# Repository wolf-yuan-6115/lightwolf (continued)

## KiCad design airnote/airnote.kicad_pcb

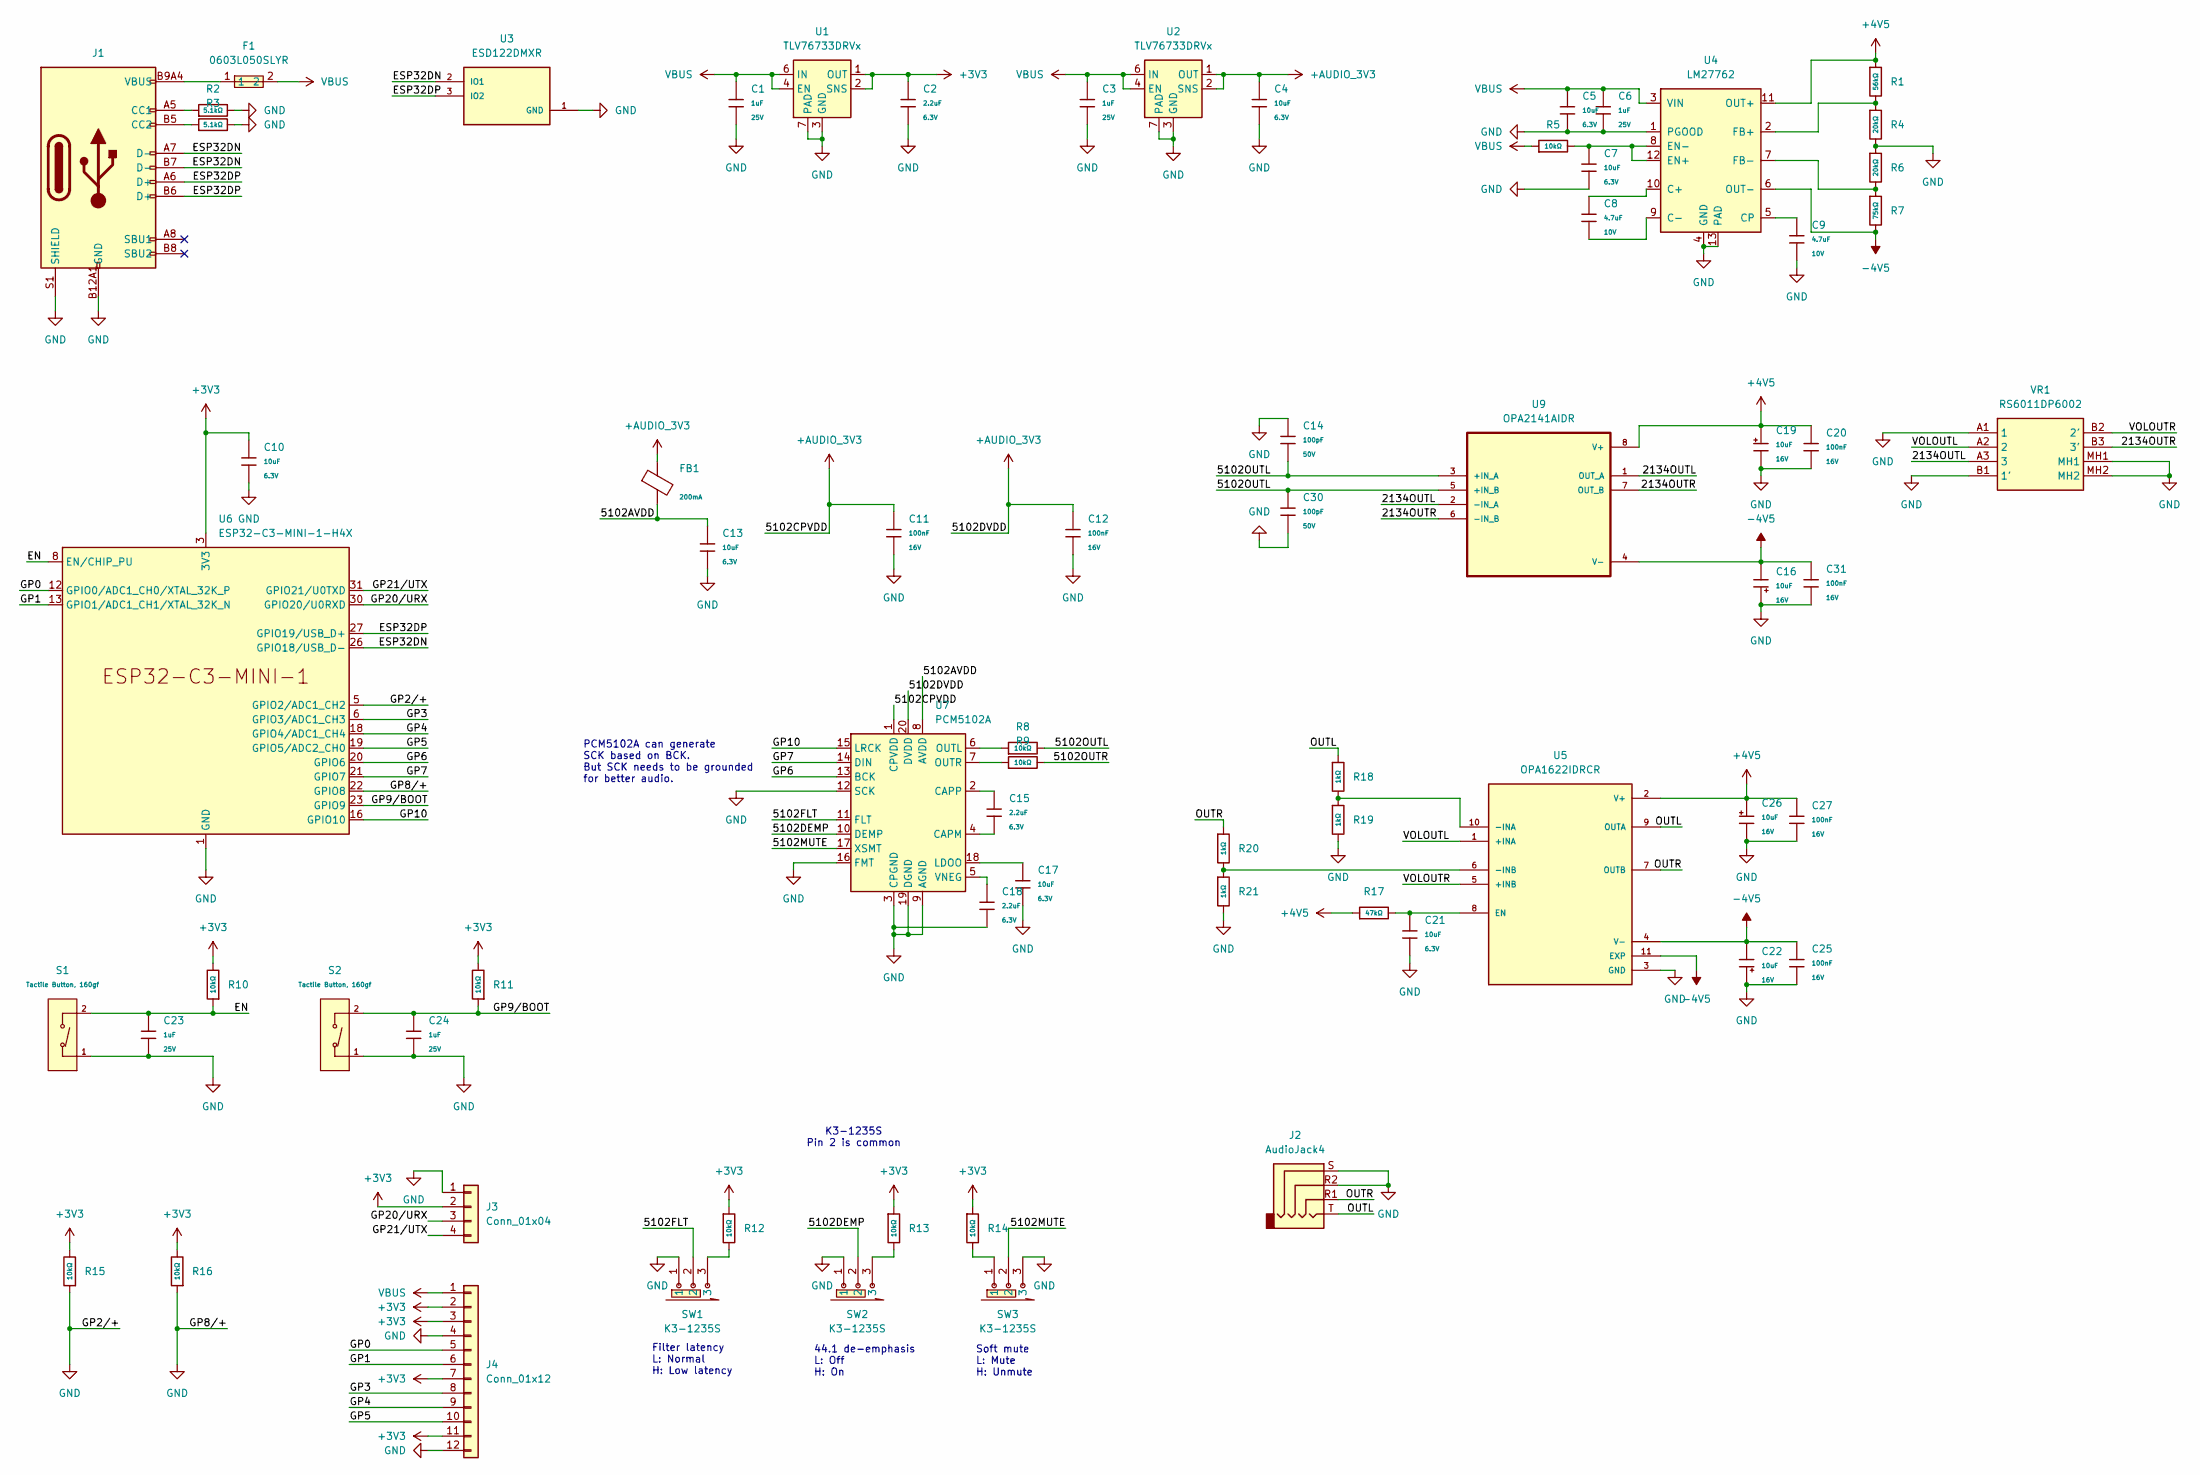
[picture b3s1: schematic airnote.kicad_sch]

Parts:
C1, C3, C6, C23, C24: 1uF; C_0402; Voltage Rated 25V; Tolerance ±10%; Part CL05A105KA5NQNC; LCSC C52923
C2, C15, C18: 2.2uF; C_0402; Voltage Rated 6.3V; Tolerance ±20%; Part CL05A225MQ5NSNC; LCSC C12530
C4, C5, C7, C10, C13, C17, C21: 10uF; C_0402; Voltage Rated 6.3V; Tolerance ±20%; Part CL05A106MQ5NUNC; LCSC C15525
C8, C9: 4.7uF; C_0402; Voltage Rated 10V; Tolerance ±20%; Part CL05A475MP5NRNC; LCSC C23733
C11, C12, C20, C25, C27, C31: 100nF; C_0402; Voltage Rated 16V; Tolerance ±10%; Part CL05B104KO5NNNC; LCSC C1525
C14, C30: 100pF; C_0402; Voltage Rated 50V; Tolerance ±5%; Part 0402CG101J500NT; LCSC C1546
C16, C19, C22, C26: 10uF; C_CASE-A-3216-18(mm); Tolerance ±10%; Rated Voltage 16V; Part TAJA106K016RNJ; LCSC C7171
F1: 0603L050SLYR; F0603; LCSC Part C207014
FB1: FB_0603; Current Rating 200mA; Tolerance ±25%; Part GZ1608D601TF; LCSC C1002
J1: Connector, USB-TYPE-C-16P; TYPE-C-SMD_HX-TYPE-C-16PIN; LCSC C5178539
J2: AudioJack4; Jack_3.5mm_KoreanHropartsElec_PJ-320D-4A_Horizontal
J3: Conn_01x04; PinHeader_1x04_P2.54mm_Vertical; LCSC C41425307
J4: Conn_01x12; PinHeader_1x12_P2.54mm_Vertical; LCSC C725944
R1: 56kΩ; R_0402; Overload Voltage (Max) 50V; Tolerance ±1%; Part 0402WGF5602TCE; LCSC C25796
R2, R3: 5.1kΩ; R_0402; Overload Voltage (Max) 50V; Tolerance ±1%; Part 0402WGF5101TCE; LCSC C25905
R4, R6: 20kΩ; R_0402; Overload Voltage (Max) 50V; Tolerance ±1%; Part 0402WGF2002TCE; LCSC C25765
R5, R8, R9, R10, R11, R12, R13, R14, R15, R16: 10kΩ; R_0402; Overload Voltage (Max) 50V; Tolerance ±1%; Part 0402WGF1002TCE; LCSC C25744
R7: 75kΩ; R_0402; Overload Voltage (Max) 50V; Tolerance ±1%; Part 0402WGF7502TCE; LCSC C25798
R17: 47kΩ; R_0402; Overload Voltage (Max) 50V; Tolerance ±1%; Part 0402WGF4702TCE; LCSC C25792
R18, R19, R20, R21: 1kΩ; R_0402; Overload Voltage (Max) 50V; Tolerance ±1%; Part 0402WGF1001TCE; LCSC C11702
S1, S2: Tactile Button, 160gf; SW_TS-1088-AR02016; Voltage Rating (Dc) 12V; Part TS-1088-AR02016; LCSC C720477
SW1, SW2, SW3: K3-1235S; SW-SMD_K3-1235S-K1; LCSC Part C92660
U1, U2: TLV76733DRVx; WSON-6-1EP_2x2mm_P0.65mm_EP1x1.6mm_ThermalVias
U3: ESD122DMXR; IC_ESD122DMXR; PARTREV A
U4: LM27762; WSON-12-1EP_3x2mm_P0.5mm_EP1x2.65_ThermalVias
U5: OPA1622IDRCR; IC_OPA1622IDRCR; PARTREV B; DigiKey_Part_Number 296-45038-1-ND
U6: ESP32-C3-MINI-1-H4X; ESP32-C3-MINI-1; LCSC C41349510
U7: PCM5102A; TSSOP-20_4.4x6.5mm_P0.65mm
U9: OPA2141AIDR; SOIC127P599X175-8N; DigiKey_Part_Number 296-41347-1-ND
VR1: RS6011DP6002; Mouser Part Number 688-RS6011DP6002

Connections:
+3V3: C2.1, C10.1, J3.2, J4.2, J4.3, J4.7, J4.11, R10.2, R11.2, R12.1, R13.1, R14.1, R15.2, R16.2, U1.1 (OUT), U1.2 (SNS), U6.3 (3V3)
+4V5: C19.1, C20.1, C26.1, C27.1, R1.1, R17.1, U4.11 (OUT+), U5.2 (V+), U9.8 (V+)
+AUDIO_3V3: C4.1, C11.1, C12.1, FB1.1, U2.1 (OUT), U2.2 (SNS), U7.1 (CPVDD), U7.20 (DVDD)
-4V5: C16.2, C22.2, C25.1, C31.1, R7.2, U4.6 (OUT-), U5.4 (V-), U5.11 (EXP), U5.12 (EXP), U5.13 (EXP), U5.14 (EXP), U5.15 (EXP), U9.4 (V-)
/2134OUTL: U9.1 (OUT_A), U9.2 (-IN_A), VR1.A3 (3)
/2134OUTR: U9.6 (-IN_B), U9.7 (OUT_B), VR1.B3 (3')
/5102AVDD: C13.1, FB1.2, U7.8 (AVDD)
/5102DEMP: SW2.2, U7.10 (DEMP)
/5102FLT: SW1.2, U7.11 (FLT)
/5102MUTE: SW3.2, U7.17 (XSMT)
/5102OUTL: C14.1, C30.2, R8.2, U9.3 (+IN_A), U9.5 (+IN_B)
/5102OUTR: R9.2
/EN: C23.1, R10.1, S1.2 (B), U6.8 (EN/CHIP_PU)
/ESP32DN: J1.A7 (D-), J1.B7 (D-), U3.2 (IO1), U6.26 (GPIO18/USB_D-)
/ESP32DP: J1.A6 (D+), J1.B6 (D+), U3.3 (IO2), U6.27 (GPIO19/USB_D+)
/GP0: J4.5, U6.12 (GPIO0/ADC1_CH0/XTAL_32K_P)
/GP1: J4.6, U6.13 (GPIO1/ADC1_CH1/XTAL_32K_N)
/GP3: J4.8, U6.6 (GPIO3/ADC1_CH3)
/GP4: J4.9, U6.18 (GPIO4/ADC1_CH4)
/GP5: J4.10, U6.19 (GPIO5/ADC2_CH0)
/GP6: U6.20 (GPIO6), U7.13 (BCK)
/GP7: U6.21 (GPIO7), U7.14 (DIN)
/GP9/BOOT: C24.1, R11.1, S2.2 (B), U6.23 (GPIO9)
/GP10: U6.16 (GPIO10), U7.15 (LRCK)
/GP20/URX: J3.3, U6.30 (GPIO20/U0RXD)
/GP21/UTX: J3.4, U6.31 (GPIO21/U0TXD)
/OUTL: J2.T, R18.1, U5.9 (OUTA)
/OUTR: J2.R1, R20.1, U5.7 (OUTB)
/VOLOUTL: U5.1 (+INA), VR1.A2 (2)
/VOLOUTR: U5.5 (+INB), VR1.B2 (2')
GND: C1.2, C2.2, C3.2, C4.2, C5.2, C6.2, C7.2, C9.2, C10.2, C11.2, C12.2, C13.2, C14.2, C16.1, C17.2, C18.2, C19.2, C20.2, C21.2, C22.1, C23.2, C24.2, C25.2, C26.2, C27.2, C30.1, C31.2, J1.A12B1 (GND), J1.B12A1 (GND), J1.S1 (SHIELD), J2.R2, J2.S, J3.1, J4.4, J4.12, R2.2, R3.2, R4.2, R6.1, R15.1, R16.1, R19.2, R21.2, S1.1 (A), S2.1 (A), SW1.1, SW2.1, SW3.3, U1.3 (GND), U1.5 (GND), U1.7 (PAD), U2.3 (GND), U2.5 (GND), U2.7 (PAD), U3.1 (GND), U4.1 (PGOOD), U4.4 (GND), U4.13 (PAD), U5.3 (GND), U6.1 (GND), U6.2 (GND), U6.5 (GPIO2/ADC1_CH2), U6.11 (GND), U6.14 (GND), U6.22 (GPIO8), U6.36 (GND), U6.37 (GND), U6.38 (GND), U6.39 (GND), U6.40 (GND), U6.41 (GND), U6.42 (GND), U6.43 (GND), U6.44 (GND), U6.45 (GND), U6.46 (GND), U6.47 (GND), U6.48 (GND), U6.49 (GND), U6.50 (GND), U6.51 (GND), U6.52 (GND), U6.53 (GND), U7.3 (CPGND), U7.9 (AGND), U7.12 (SCK), U7.16 (FMT), U7.19 (DGND), VR1.A1 (1), VR1.B1 (1'), VR1.MH1, VR1.MH2
unnamed: F1.1, J1.A9B4 (VBUS), J1.B9A4 (VBUS)
unnamed: J1.A5 (CC1), R2.1
unnamed: J1.B5 (CC2), R3.1
unnamed: R12.2, SW1.3
unnamed: R13.2, SW2.3
unnamed: R14.2, SW3.1
unnamed: C8.1, U4.10 (C+)
unnamed: C8.2, U4.9 (C-)
unnamed: C9.1, U4.5 (CP)
unnamed: C7.1, R5.2, U4.8 (EN-), U4.12 (EN+)
unnamed: R1.2, R4.1, U4.2 (FB+)
unnamed: R6.2, R7.1, U4.7 (FB-)
unnamed: R18.2, R19.1, U5.10 (-INA)
unnamed: R20.2, R21.1, U5.6 (-INB)
unnamed: C21.1, R17.2, U5.8 (EN)
unnamed: C15.2, U7.4 (CAPM)
unnamed: C15.1, U7.2 (CAPP)
unnamed: C17.1, U7.18 (LDOO)
unnamed: R8.1, U7.6 (OUTL)
unnamed: R9.1, U7.7 (OUTR)
unnamed: C18.1, U7.5 (VNEG)
VBUS: C1.1, C3.1, C5.1, C6.1, F1.2, J4.1, R5.1, U1.4 (EN), U1.6 (IN), U2.4 (EN), U2.6 (IN), U4.3 (VIN)

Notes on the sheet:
44.1 de-emphasis L: Off H: On
Soft mute L: Mute H: Unmute
K3-1235S Pin 2 is common
Filter latency L: Normal H: Low latency
PCM5102A can generate SCK based on BCK. But SCK needs to be grounded for better audio.

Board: 4 copper layers, 70 parts (0 on the bottom side), 52 nets, no tracks yet.

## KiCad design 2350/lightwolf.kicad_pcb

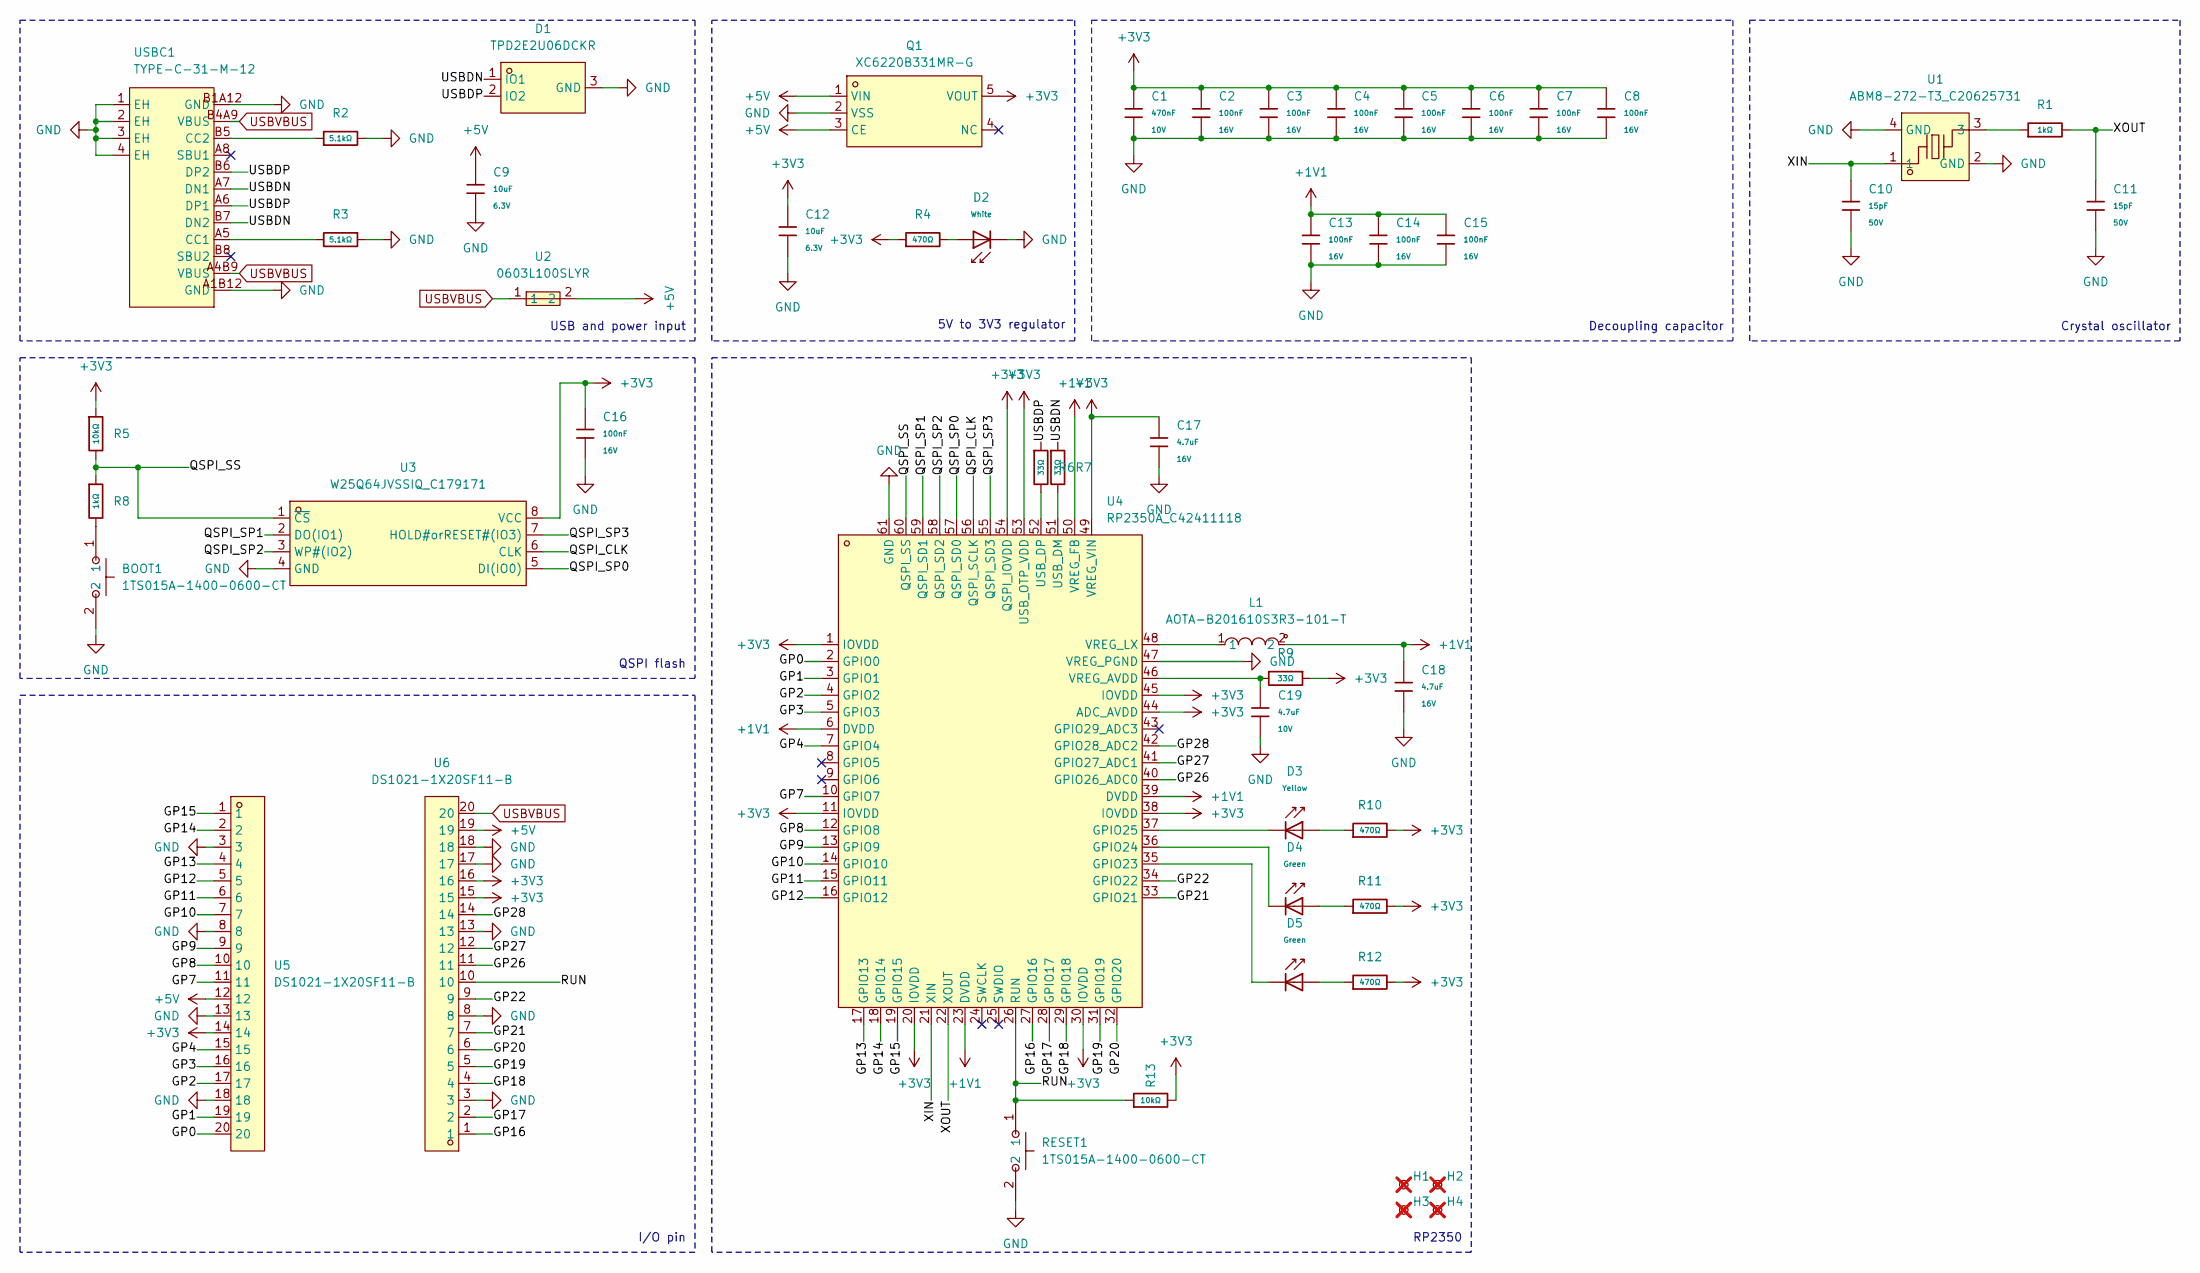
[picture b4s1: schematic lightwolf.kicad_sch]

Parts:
BOOT1: 1TS015A-1400-0600-CT; SW-SMD_L3.0-W2.0-LS3.5; LCSC Part C319433
C1: 470nF; C_0402; Voltage Rated 10V; Tolerance ±10%; Part CL05A474KP5NNNC; LCSC C47339
C2, C3, C4, C5, C6, C7, C8, C13, C14, C15, C16: 100nF; C_0402; Voltage Rated 16V; Tolerance ±10%; Part CL05B104KO5NNNC; LCSC C1525
C9, C12: 10uF; C_0402; Voltage Rated 6.3V; Tolerance ±20%; Part CL05A106MQ5NUNC; LCSC C15525
C10, C11: 15pF; C_0402; Voltage Rated 50V; Tolerance ±5%; Part 0402CG150J500NT; LCSC C1548
C17, C18: 4.7uF; C_0603; Voltage Rated 16V; Tolerance ±10%; Part CL10A475KO8NNNC; LCSC C19666
C19: 4.7uF; C_0402; Voltage Rated 10V; Tolerance ±20%; Part CL05A475MP5NRNC; LCSC C23733
D1: TPD2E2U06DCKR; SC-70-3_L2.0-W1.3-P0.65-LS2.1-BL; LCSC Part C1855726
D2: White; D_0603; Part KT-0603W; LCSC C2290
D3: Yellow; D_0805; Part KT-0805Y; LCSC C2296
D4, D5: Green; D_0805; Part KT-0805G; LCSC C2297
H1, H2, H3, H4: Hole_Tooling_JLCPCB; not fitted
L1: AOTA-B201610S3R3-101-T; IND-SMD_L2.0-W1.6_AOTA-B201610S3R3-101-T; LCSC Part C42411119
Q1: XC6220B331MR-G; SOT-25_L3.0-W1.6-P0.95-LS2.8-TL; LCSC Part C86534
R1, R8: 1kΩ; R_0402; Overload Voltage (Max) 50V; Tolerance ±1%; Part 0402WGF1001TCE; LCSC C11702
R2, R3: 5.1kΩ; R_0402; Overload Voltage (Max) 50V; Tolerance ±1%; Part 0402WGF5101TCE; LCSC C25905
R4, R10, R11, R12: 470Ω; R_0402; Overload Voltage (Max) 50V; Tolerance ±1%; Part 0402WGF4700TCE; LCSC C25117
R5, R13: 10kΩ; R_0402; Overload Voltage (Max) 50V; Tolerance ±1%; Part 0402WGF1002TCE; LCSC C25744
R6, R7, R9: 33Ω; R_0402; Overload Voltage (Max) 50V; Tolerance ±1%; Part 0402WGF330JTCE; LCSC C25105
RESET1: 1TS015A-1400-0600-CT; SW-SMD_L3.0-W2.0-LS3.5; LCSC Part C319433
U1: ABM8-272-T3_C20625731; CRYSTAL-SMD_4P-L3.2-W2.5-BL; LCSC Part C20625731
U2: 0603L100SLYR; R0603; LCSC Part C207017
U3: W25Q64JVSSIQ_C179171; SOIC-8_L5.3-W5.3-P1.27-LS8.0-BL; LCSC Part C179171
U4: RP2350A_C42411118; QFN-60-1EP_7x7mm_P0.4mm_EP3.4x3.4mm_ThermalVias; LCSC Part C42411118
U5, U6: DS1021-1X20SF11-B; HDR-TH_20P-P2.54-V-M; LCSC Part C7430376
USBC1: TYPE-C-31-M-12; USB-C_SMD-TYPE-C-31-M-12_1; LCSC Part C165948

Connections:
+1V1: C13.1, C14.1, C15.1, C18.1, L1.2, U4.6 (DVDD), U4.23 (DVDD), U4.39 (DVDD), U4.50 (VREG_FB)
+3V3: C1.1, C2.1, C3.1, C4.1, C5.1, C6.1, C7.1, C8.1, C12.1, C16.1, C17.1, Q1.5 (VOUT), R4.1, R5.1, R9.1, R10.2, R11.2, R12.2, R13.2, U3.8 (VCC), U4.1 (IOVDD), U4.11 (IOVDD), U4.20 (IOVDD), U4.30 (IOVDD), U4.38 (IOVDD), U4.44 (ADC_AVDD), U4.45 (IOVDD), U4.49 (VREG_VIN), U4.53 (USB_OTP_VDD), U4.54 (QSPI_IOVDD), U5.14, U6.15, U6.16
+5V: C9.1, Q1.1 (VIN), Q1.3 (CE), U2.2, U5.12, U6.19
/GP0: U4.2 (GPIO0), U5.20
/GP1: U4.3 (GPIO1), U5.19
/GP2: U4.4 (GPIO2), U5.17
/GP3: U4.5 (GPIO3), U5.16
/GP4: U4.7 (GPIO4), U5.15
/GP7: U4.10 (GPIO7), U5.11
/GP8: U4.12 (GPIO8), U5.10
/GP9: U4.13 (GPIO9), U5.9
/GP10: U4.14 (GPIO10), U5.7
/GP11: U4.15 (GPIO11), U5.6
/GP12: U4.16 (GPIO12), U5.5
/GP13: U4.17 (GPIO13), U5.4
/GP14: U4.18 (GPIO14), U5.2
/GP15: U4.19 (GPIO15), U5.1
/GP16: U4.27 (GPIO16), U6.1
/GP17: U4.28 (GPIO17), U6.2
/GP18: U4.29 (GPIO18), U6.4
/GP19: U4.31 (GPIO19), U6.5
/GP20: U4.32 (GPIO20), U6.6
/GP21: U4.33 (GPIO21), U6.7
/GP22: U4.34 (GPIO22), U6.9
/GP26: U4.40 (GPIO26_ADC0), U6.11
/GP27: U4.41 (GPIO27_ADC1), U6.12
/GP28: U4.42 (GPIO28_ADC2), U6.14
/QSPI_CLK: U3.6 (CLK), U4.56 (QSPI_SCLK)
/QSPI_SP0: U3.5 (DI(IO0)), U4.57 (QSPI_SD0)
/QSPI_SP1: U3.2 (DO(IO1)), U4.59 (QSPI_SD1)
/QSPI_SP2: U3.3 (WP#(IO2)), U4.58 (QSPI_SD2)
/QSPI_SP3: U3.7 (HOLD#orRESET#(IO3)), U4.55 (QSPI_SD3)
/QSPI_SS: R5.2, R8.1, U3.1 (~CS), U4.60 (QSPI_SS)
/RUN: R13.1, RESET1.1, U4.26 (RUN), U6.10
/USBDN: D1.1 (IO1), R7.1, USBC1.A7 (DN1), USBC1.B7 (DN2)
/USBDP: D1.2 (IO2), R6.1, USBC1.A6 (DP1), USBC1.B6 (DP2)
/XIN: C10.1, U1.1, U4.21 (XIN)
/XOUT: C11.1, R1.2, U4.22 (XOUT)
GND: BOOT1.2, C1.2, C2.2, C3.2, C4.2, C5.2, C6.2, C7.2, C8.2, C9.2, C10.2, C11.2, C12.2, C13.2, C14.2, C15.2, C16.2, C17.2, C18.2, C19.2, D1.3 (GND), D2.1, Q1.2 (VSS), R2.2, R3.1, RESET1.2, U1.2 (GND), U1.4 (GND), U3.4 (GND), U4.47 (VREG_PGND), U4.61 (GND), U5.3, U5.8, U5.13, U5.18, U6.3, U6.8, U6.13, U6.17, U6.18, USBC1.1 (EH), USBC1.2 (EH), USBC1.3 (EH), USBC1.4 (EH), USBC1.A1B12 (GND), USBC1.B1A12 (GND)
unnamed: BOOT1.1, R8.2
unnamed: D2.2, R4.2
unnamed: D3.2, R10.1
unnamed: D4.2, R11.1
unnamed: D5.2, R12.1
unnamed: R1.1, U1.3
unnamed: D5.1, U4.35 (GPIO23)
unnamed: D4.1, U4.36 (GPIO24)
unnamed: D3.1, U4.37 (GPIO25)
unnamed: R7.2, U4.51 (USB_DM)
unnamed: R6.2, U4.52 (USB_DP)
unnamed: C19.1, R9.2, U4.46 (VREG_AVDD)
unnamed: L1.1, U4.48 (VREG_LX)
unnamed: R3.2, USBC1.A5 (CC1)
unnamed: R2.1, USBC1.B5 (CC2)
USBVBUS: U2.1, U6.20, USBC1.A4B9 (VBUS), USBC1.B4A9 (VBUS)

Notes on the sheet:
QSPI flash
Decoupling capacitor
5V to 3V3 regulator
RP2350
Crystal oscillator
USB and power input
I/O pin

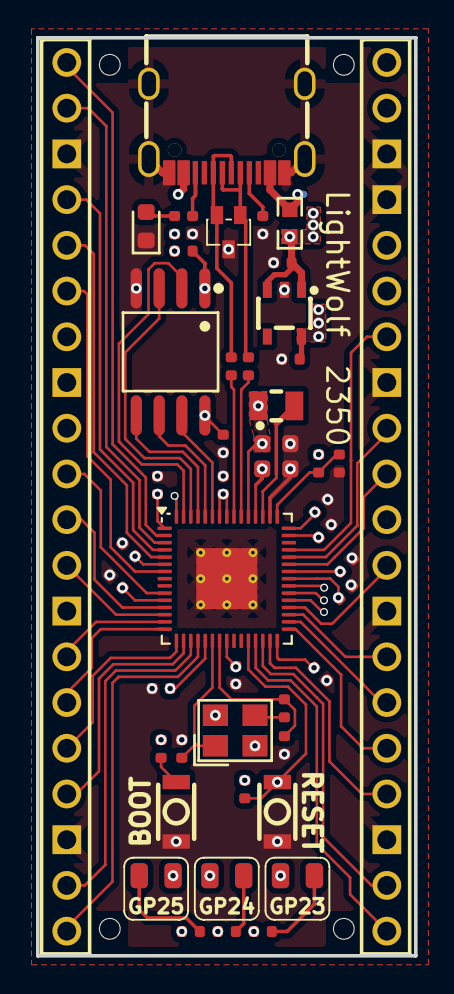
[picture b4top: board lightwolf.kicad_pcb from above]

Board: 4 copper layers, 21.0 x 51.0 mm, 52 parts (0 on the bottom side), 55 nets.

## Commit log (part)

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2025-10-23 feat: add LightWolf 2350
2025-10-23 docs: update readme
2025-10-23 feat: update design files and add production files
2025-10-23 feat: add blueprint files
2025-10-23 feat: add cart photo and update bom
2025-10-23 chore: remove cart picture
2025-10-26 fix: design issue and update project files
2025-10-31 fix: decoupling issue for VREG_AVDD
2026-02-03 chore: create journal.md
2026-02-03 chore: move 2350 journal
2026-02-05 feat: airnote journal update
2026-02-13 feat: upload kicad design source files
2026-02-22 feat: airnote journal update (realized I've copying wrong message for a while)
2026-02-22 feat: rename airnote to pumper and update kicad sources
2026-02-22 feat: pumper journal update
2026-02-24 feat: update kicad source files
2026-02-24 feat: add image
2026-03-05 feat: update design files
2026-03-06 feat: built experimental firmware
2026-03-06 feat: update kicad files
2026-04-02 feat: update firmware for pumper
2026-04-02 fix: left and right channel reversed
2026-04-06 feat: use blue led for audio level indicator
2026-04-18 feat: update blue led behavior
2026-04-28 Fix ring buffer comment: max sample rate is 192kHz, not 96kHz
    Agent-Logs-Url: https://github.com/wolf-yuan-6115/lightwolf/sessions/820f3689-2539-4cb6-b376-8353f344414f
2026-04-28 Add comments to all remaining firmware source files
    Agent-Logs-Url: https://github.com/wolf-yuan-6115/lightwolf/sessions/820f3689-2539-4cb6-b376-8353f344414f
2026-04-28 Fix RP2040 references: board is RP2350
    Agent-Logs-Url: https://github.com/wolf-yuan-6115/lightwolf/sessions/717f7b5f-2044-4010-a480-f08d67685607
2026-04-28 feat: add license
2026-05-12 feat: add feather
2026-05-12 feat: feather production files
2026-05-12 feat: feather assets
2026-05-12 feat: got some eq
2026-05-12 feat: make changes to eq
2026-05-12 feat: feather firmware
2026-05-12 feat: update pcb design and layout
2026-05-12 fix: oops forget to connect 3v3 to led
2026-05-13 feat: update board design
2026-05-13 feat: update power line trace width
2026-05-13 feat: update feather design files
2026-05-13 feat: update jlcpcb production files
2026-05-16 feat: add some more detail to readme
2026-05-16 feat: increase pumper led level
2026-05-16 feat: update firmware to new board design
2026-05-16 feat: add two more buttons
2026-05-19 feat: add real image
